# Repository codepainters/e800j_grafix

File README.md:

# Elwro 800 Junior - GraFIX

The purpose of this tiny project is to fix a design flaw in the [Elwro 800 Junior](https://pl.wikipedia.org/wiki/Elwro_800_Junior) that causes visible graphical artifacts.

In this repo:

* schematic/PCB project in KiCAD 8 format (in this very directory)
* PDF schematics - [color](grafix_sch.pdf) and [black&white](grafix_sch_bw.pdf)
* [interactive BOM](grafix_ibom.html) file (you have to download it and open locally)
* Gerber files (in a [jlcpcb](https://jlcpcb.com/)-compatible ZIP format):
  * [grafix.zip](gerbers/grafix.zip) - single PCB
  * [grafix_2x_panel.zip](gerbers/grafix_2x_panel.zip) - two PCBs panelized

## The problem & solution

The pictures below were taken before and after installing the `GraFIX` PCB. . In the first screenshot, green and blue artifacts are clearly visible around the green letters (other examples [here](img)). 

Junior uses the same screen organization as the ZX Spectrum - every consecutive group of 8 pixels shares the same ink and paper color pair, the pixel value determines whether it is displayed in the ink or paper color. Junior employs two `74LS153` multiplexers for the color selection, this is a purely combinatorial circuit, unfortunately, leading to occasional short (~30ns) glitches visible as artifacts.

Fortunately, the multiplexer outputs remain stable around the rising edges of the `CKPIX` (pixel clock) signal. The `GraFIX` mod adds a 4-bit register (`74LS175`) at the multiplexer outputs, clocked by `CKPIX` (pixel clock) signal. This effectively latches a stable color value for each pixel, eliminating the glitches.

## Assembling

When soldering the PCB, follow this order: pin headers under `U2`, then `U2` itself, followed by pin headers under `U1`, and finally `U1`. Soldering all the pin headers first makes it difficult to solder pins 9 to 16 of `U2` due to the small gap between the inner pin headers (been there, done that). See below:

Then you have to unsolder `74LS153` multiplexers and replace them with `DIL-16` sockets, now you can insert `GraFIX` PCB into the sockets. The last step is to connect `J3` header on the `GraFIX` board to `CKPIX` signal on the Junior PCB with a short piece of wire. The best place to do it is a via close to `R38`, marked with red `X`. That's it!

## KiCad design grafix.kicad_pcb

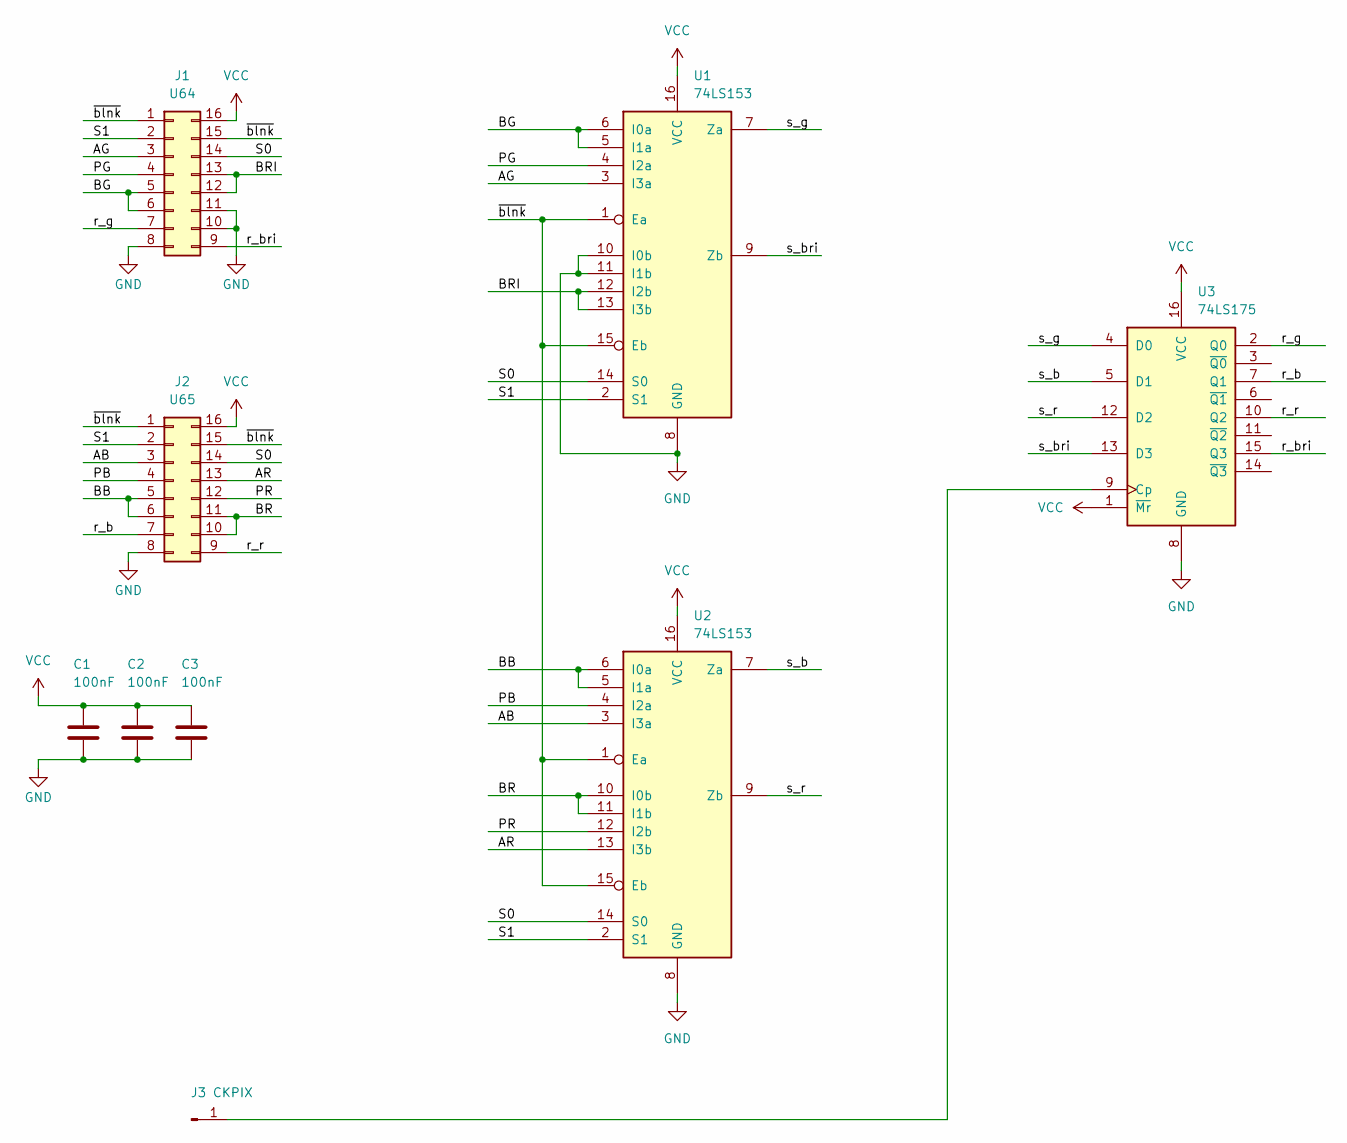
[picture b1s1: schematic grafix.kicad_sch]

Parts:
C1, C2, C3: 100nF; C_Disc_D5.0mm_W2.5mm_P5.00mm
J1: U64; DIP16_pins
J2: U65; DIP16_pins
J3: CKPIX; PinHeader_1x01_P2.00mm_Vertical
U1, U2: 74LS153; DIP-16_W7.62mm
U3: 74LS175; DIP-16_W7.62mm

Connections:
/AB: J2.3, U2.3 (I3a)
/AG: J1.3, U1.3 (I3a)
/AR: J2.13, U2.13 (I3b)
/BB: J2.5, J2.6, U2.5 (I1a), U2.6 (I0a)
/BG: J1.5, J1.6, U1.5 (I1a), U1.6 (I0a)
/BR: J2.10, J2.11, U2.10 (I0b), U2.11 (I1b)
/BRI: J1.12, J1.13, U1.12 (I2b), U1.13 (I3b)
/PB: J2.4, U2.4 (I2a)
/PG: J1.4, U1.4 (I2a)
/PR: J2.12, U2.12 (I2b)
/S0: J1.14, J2.14, U1.14 (S0), U2.14 (S0)
/S1: J1.2, J2.2, U1.2 (S1), U2.2 (S1)
/r_b: J2.7, U3.7 (Q1)
/r_bri: J1.9, U3.15 (Q3)
/r_g: J1.7, U3.2 (Q0)
/r_r: J2.9, U3.10 (Q2)
/s_b: U2.7 (Za), U3.5 (D1)
/s_bri: U1.9 (Zb), U3.13 (D3)
/s_g: U1.7 (Za), U3.4 (D0)
/s_r: U2.9 (Zb), U3.12 (D2)
/~blnk: J1.1, J1.15, J2.1, J2.15, U1.1 (Ea), U1.15 (Eb), U2.1 (Ea), U2.15 (Eb)
GND: C1.2, C2.2, C3.2, J1.8, J1.10, J1.11, J2.8, U1.8 (GND), U1.10 (I0b), U1.11 (I1b), U2.8 (GND), U3.8 (GND)
unnamed: J3.1, U3.9 (Cp)
VCC: C1.1, C2.1, C3.1, J1.16, J2.16, U1.16 (VCC), U2.16 (VCC), U3.1 (~Mr), U3.16 (VCC)

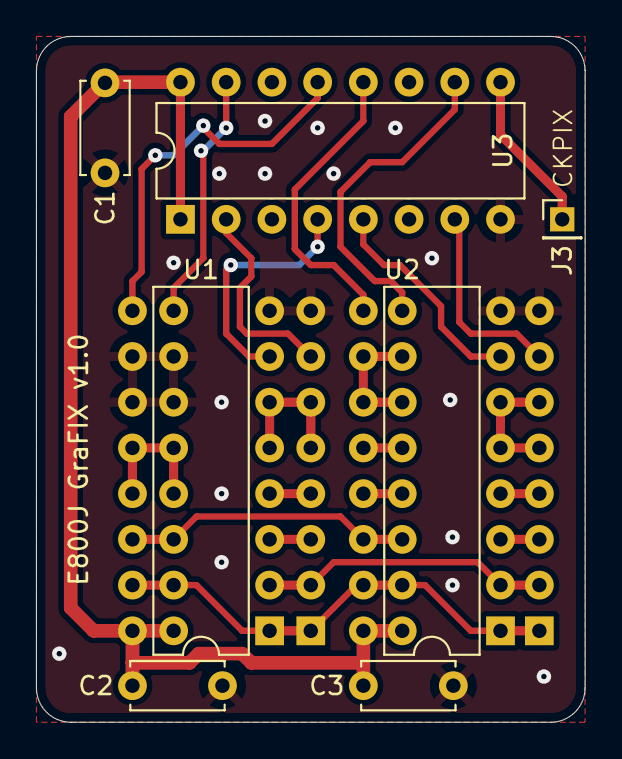
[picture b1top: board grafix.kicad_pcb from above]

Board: 2 copper layers, 30.5 x 38.1 mm, 9 parts (0 on the bottom side), 24 nets.

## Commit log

2025-01-14 Bootstrapping.
2025-01-15 Initial version.
2025-01-15 Minor tweaks
2025-02-01 Added interactive BOM.
    Closes #3
2025-02-01 Minor schematic fix
2025-02-01 Schematic as PDF
    Closes #2
2025-02-01 Added gerbers for regular and 2x planel versions
2025-02-11 Added images
2025-02-11 README sketch
2025-02-12 README completed
2025-02-12 README - minor edits
